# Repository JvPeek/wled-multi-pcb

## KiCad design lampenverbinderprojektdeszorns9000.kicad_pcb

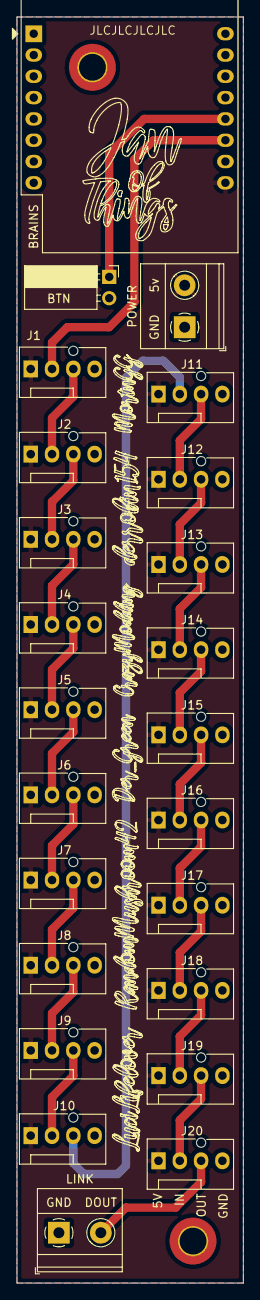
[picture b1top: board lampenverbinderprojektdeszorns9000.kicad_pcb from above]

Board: 2 copper layers, 27.0 x 151.0 mm, 26 parts (0 on the bottom side), 24 nets.

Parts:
BRAINS: WeMos_D1_mini; WEMOS_D1_mini_light
BTN: SW_Push; PinSocket_1x02_P2.54mm_Horizontal
H1, H2: MountingHole_Pad; MountingHole_3.2mm_M3_DIN965_Pad_TopBottom
J1, J2, J3, J4, J5, J6, J7, J8, J9, J10, J11, J12, J13, J14, J15, J16, J17, J18, J19, J20: Conn_01x04_Male; FanPinHeader_1x04_P2.54mm_Vertical
LINK: Screw_Terminal_01x02; TerminalBlock_Phoenix_MKDS-1,5-2_1x02_P5.00mm_Horizontal
POWER: Screw_Terminal_01x02; TerminalBlock_Phoenix_MKDS-1,5-2_1x02_P5.00mm_Horizontal

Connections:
+5V: BRAINS.9, J1.1, J2.1, J3.1, J4.1, J5.1, J6.1, J7.1, J8.1, J9.1, J10.1, J11.1, J12.1, J13.1, J14.1, J15.1, J16.1, J17.1, J18.1, J19.1, J20.1, POWER.2
/DOUT: BRAINS.11, J1.2
GND: BRAINS.10, BTN.2, H1.1, H2.1, J1.4, J2.4, J3.4, J4.4, J5.4, J6.4, J7.4, J8.4, J9.4, J10.4, J11.4, J12.4, J13.4, J14.4, J15.4, J16.4, J17.4, J18.4, J19.4, J20.4, LINK.1, POWER.1
unnamed: J1.3, J2.2
unnamed: J2.3, J3.2
unnamed: J3.3, J4.2
unnamed: J4.3, J5.2
unnamed: J5.3, J6.2
unnamed: J6.3, J7.2
unnamed: J7.3, J8.2
unnamed: J8.3, J9.2
unnamed: J9.3, J10.2
unnamed: J10.3, J11.2
unnamed: J11.3, J12.2
unnamed: J12.3, J13.2
unnamed: J13.3, J14.2
unnamed: J14.3, J15.2
unnamed: J15.3, J16.2
unnamed: J16.3, J17.2
unnamed: J17.3, J18.2
unnamed: J18.3, J19.2
unnamed: J19.3, J20.2
unnamed: J20.3, LINK.2
unnamed: BRAINS.12, BTN.1

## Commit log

2022-01-14 just throw it onto github they said. it will be easy they said.
